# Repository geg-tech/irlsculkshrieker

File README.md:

# IRL Sculk Shrieker

This is a recreation of the [***sculk shrieker***](https://minecraft.wiki/w/Sculk_Shrieker) from the game Minecraft, made for Highway!

This block will ~~summon a warden at your exact location~~ shriek whenever it hears a sound nearby through a speaker embedded inside the top of the shrieker. Perfect for alarming anyone sneaking past you and inflicting [*severe ancient city flashbacks*](https://github.com/geg-tech/irlsculkshrieker/blob/main/extras/flashbacks.png) onto friends!

I made this project as my last Highway submission, and wanted to end off with something that *wasn't* another keyboard. I saw the Minecraft submissions by [@aaron huang and his compass](https://github.com/RunTheBot/Compasses-Were-Copied-From-Minecraft) and by [@danieliscrazy and his jukebox](https://github.com/danieliscrazy/Jukebox), and was inspired to make my own Minecraft-related project, which soon grew into this sculk shrieker. <br/>

I aimed to be as *game accurate* as possible while also putting my own spin on the design, using the textures as reference when detailing and modeling the case and incorporating little features and details into the final result, such as the animated textures on the top of the block. Every pixel on the texture translates to 4mm on the model, making the entire shrieker have a tiny footprint of *64mm x 64mm! wow!* 

*features:*
* 3D game accurate model with separated components to be as easy to paint as possible
* shrieker audio taken from the game, which can be changed via micro SD
* animated RGB ring to simulate the animated souls on the top of the block
* tiny 64mm x 64mm footprint

## CAD

## PCB + Wiring Diagram
### Wiring Diagram
 <br/>
### PCB
 <br/>
 <br/>
 <br/>

## BOM
|name|quantity|price|link|source|
|---|---|---|---|---|
|Micro SD SPI/SDIO Breakout Board|x1|$1.16|[here](https://www.aliexpress.us/item/3256807025102697.html?spm=a2g0o.productlist.main.22.76062979sv16Ys&aem_p4p_detail=202507091234296877204339592160001470840&algo_pvid=2704982b-dbc3-4469-bc09-b28713b35cae&algo_exp_id=2704982b-dbc3-4469-bc09-b28713b35cae-19&pdp_ext_f=%7B%22order%22%3A%22156%22%2C%22eval%22%3A%221%22%7D&pdp_npi=4%40dis%21USD%211.99%211.94%21%21%2114.22%2113.83%21%4021030ea417520896694654841ebaa9%2112000039821817298%21sea%21US%216388337753%21X&curPageLogUid=vFXRvpeSNyqn&utparam-url=scene%3Asearch%7Cquery_from%3A&search_p4p_id=202507091234296877204339592160001470840_5#nav-specification)|Aliexpress|
|Individual SMD SK6812RGBW|x20|$4.18|[here](https://www.aliexpress.us/item/2251832437268792.html?spm=a2g0o.productlist.main.21.5d88GqqjGqqjJ1&algo_pvid=360120fd-e970-4f8d-8365-b130bf63ae4a&algo_exp_id=360120fd-e970-4f8d-8365-b130bf63ae4a-18&pdp_ext_f=%7B%22order%22%3A%22123%22%2C%22eval%22%3A%221%22%7D&pdp_npi=4%40dis%21USD%219.50%216.00%21%21%219.50%216.00%21%4021030ea417520894030141830ebac8%2112000038353355770%21sea%21US%216388337753%21X&curPageLogUid=6T9DOaEms7fh&utparam-url=scene%3Asearch%7Cquery_from%3A)|Aliexpress|
|4 Ohm 3 Watt Speaker|x1|$2.95|[here](https://www.aliexpress.us/item/3256805513376202.html?spm=a2g0o.detail.0.0.e91d8P9I8P9IvQ&mp=1&pdp_npi=5%40dis%21USD%21USD%202.95%21USD%202.81%21%21USD%202.81%21%21%21%402101ef7017517659888774051ebce8%2112000037280015644%21ct%21US%216388337753%21%211%210&gatewayAdapt=glo2usa)|Aliexpress|
|KY-037 Sound Sensor|x1|$1.04|[here](https://www.aliexpress.us/item/3256807347494500.html?spm=a2g0o.detail.0.0.542aLwRHLwRHNI&mp=1&pdp_npi=5%40dis%21USD%21USD%202.92%21USD%202.92%21%21USD%202.92%21%21%21%402103244617517664615985016e6b67%2112000041188403861%21ct%21US%216388337753%21%211%210&gatewayAdapt=glo2usa)|Aliexpress|
|ESP32|x1|$3.98|[here](https://www.aliexpress.us/item/3256807453968983.html?spm=a2g0o.detail.0.0.4443wfd1wfd1Kn&mp=1&pdp_npi=5%40dis%21USD%21USD%203.98%21USD%203.64%21%21USD%203.64%21%21%21%402103246617517664681434438e1056%2112000041608696464%21ct%21US%216388337753%21%211%210&gatewayAdapt=glo2usa)|Aliexpress|
|MAX98357A Speaker Amp|x1|$1.66|[here](https://www.aliexpress.us/item/3256806882501015.html?spm=a2g0o.detail.0.0.7a781pAH1pAHw5&mp=1&pdp_npi=5%40dis%21USD%21USD%201.84%21USD%201.80%21%21USD%201.80%21%21%21%402103277f17517664746265268e3da2%2112000039302356100%21ct%21US%216388337753%21%211%210&gatewayAdapt=glo2usa)|Aliexpress|
|PCB|x1|$2.00| |JLCPCB|
|Case (all parts)|x1|$0.00| |3D printing|
|M2 Screws|x4 16mm, x2 10mm|$0.00| | Already Owned|
|Paint|x1|$0.00| | Already Owned|
|Cable|x1|$0.00| | Already Owned|
|Soldering Iron + Solder wire + Flux|x1|$0.00| | Already Owned|
|Solid Core Wire|x1|$0.00| | Already Owned|
|Hot Glue|x1|$0.00| | Already Owned|
| | | | | |
|Subtotal: $27.03| | | | |
| Aliexpress: $16.91 | JLCPCB: $8.12 | | | |
| Total: **$25.03** | | | | |

## notes/extras
Neopixels and the SD card module were sourced from Adafruit to package the shipping/tax together:
* The Adafruit SD card module is specifically rated for 3V, ensuring that it doesn't blow up the esp32

* huge thanks to [@aaron huang](https://github.com/RunTheBot/Compasses-Were-Copied-From-Minecraft) and [@danieliscrazy](https://github.com/danieliscrazy/Jukebox) for their respective projects and inspiring me to make something from Minecraft
* shout out to the people behind the (*actually good*) [Minecraft Wiki](https://minecraft.wiki/w/Sculk_Shrieker), which hosted the textures for the sculk shrieker for myself to use
* the person behind [DroneBotWorkshop](https://dronebotworkshop.com/esp32-i2s/), which provided helpful reference for setting up the firmware
* the people behind highway (as always :3)

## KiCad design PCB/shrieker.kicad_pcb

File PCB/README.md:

# welcome to the pcb store
what can i get for you today

 <br/>
 <br/>
 <br/>
 <br/>

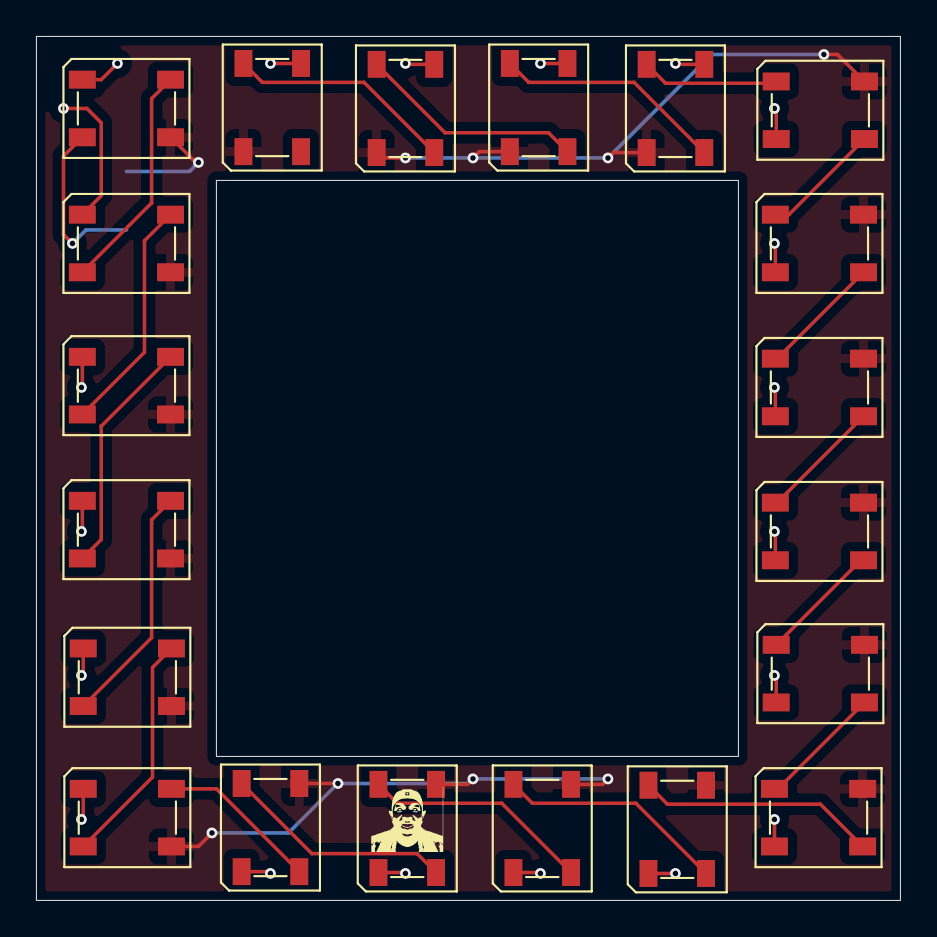
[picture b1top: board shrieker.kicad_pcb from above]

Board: 2 copper layers, 48.0 x 48.0 mm, 20 parts (0 on the bottom side), 21 nets.

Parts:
D1, D2, D3, D4, D5, D6, D7, D8, D9, D10, D11, D12, D13, D14, D15, D16, D17, D18, D19, D20: SK6812; LED_SK6812_PLCC4_5.0x5.0mm_P3.2mm

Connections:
+3.3V: D1.3 (VDD), D2.3 (VDD), D3.3 (VDD), D4.3 (VDD), D5.3 (VDD), D6.3 (VDD), D7.3 (VDD), D8.3 (VDD), D9.3 (VDD), D10.3 (VDD), D11.4 (DOUT), D12.4 (DOUT), D13.4 (DOUT), D14.4 (DOUT), D15.4 (DOUT), D16.4 (DOUT), D17.1 (VSS), D18.1 (VSS), D19.1 (VSS), D20.1 (VSS)
GND: D1.1 (VSS), D2.1 (VSS), D3.1 (VSS), D4.1 (VSS), D5.1 (VSS), D6.1 (VSS), D7.1 (VSS), D8.1 (VSS), D9.1 (VSS), D10.1 (VSS), D11.2 (DIN), D12.2 (DIN), D13.2 (DIN), D14.2 (DIN), D15.2 (DIN), D16.2 (DIN), D17.3 (VDD), D18.3 (VDD), D19.3 (VDD), D20.3 (VDD)
unnamed: D1.4 (DOUT), D2.2 (DIN)
unnamed: D2.4 (DOUT), D3.2 (DIN)
unnamed: D3.4 (DOUT), D4.2 (DIN)
unnamed: D4.4 (DOUT), D5.2 (DIN)
unnamed: D5.4 (DOUT), D6.2 (DIN)
unnamed: D6.4 (DOUT), D7.2 (DIN)
unnamed: D7.4 (DOUT), D8.2 (DIN)
unnamed: D8.4 (DOUT), D9.2 (DIN)
unnamed: D9.4 (DOUT), D10.2 (DIN)
unnamed: D10.4 (DOUT), D11.3 (VDD)
unnamed: D11.1 (VSS), D12.3 (VDD)
unnamed: D12.1 (VSS), D13.3 (VDD)
unnamed: D13.1 (VSS), D14.3 (VDD)
unnamed: D14.1 (VSS), D15.3 (VDD)
unnamed: D15.1 (VSS), D16.3 (VDD)
unnamed: D16.1 (VSS), D17.4 (DOUT)
unnamed: D17.2 (DIN), D18.4 (DOUT)
unnamed: D18.2 (DIN), D19.4 (DOUT)
unnamed: D19.2 (DIN), D20.4 (DOUT)

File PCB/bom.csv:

Designator,Footprint,Quantity,Value,LCSC Part #
"D1, D10, D11, D12, D13, D14, D15, D16, D17, D18, D19, D2, D20, D3, D4, D5, D6, D7, D8, D9",LED_SK6812_PLCC4_5.0x5.0mm_P3.2mm,20,SK6812,

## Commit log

2025-07-08 Rename shrieker.step to pcb.step
